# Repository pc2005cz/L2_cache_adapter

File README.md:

NOTICE this is just an untested proof of concept

# 486 L2 cache adapter for TSOP32/DIP32

Asynchronous fast SRAM chips in DIP32 package, were phased out. This makes not possible to use new chips to upgrade 486 L2 cache. However there are still compatible SRAM variants in SMT packages.

This project aims to create a PCB design, which allows the retro community to put TSOP32 chip into a DIP32 socket.

# Design

DIP32 sockets usually have the absolute maximum dimensions 10 x 40 mm. The adapter need to be less wide than that (and any exceeding PCB space due to a manufacturing tolerances needs to be sanded out).

TSOP32 type I chips needs to have width below this limit too. This reduces the list of possible chips only few types. Also there is a difference between 3.3V and 5V SRAM pinouts. The 3.3V pinouts would be highly complicated to route on 2 layer PCB.

The resulting list of chips I've found is:

* IS61C1024AL-12TLI
* CY7C109D-10ZXI
* AS7C1024B-12TCN

These chips have dimensions around 8 x 20 mm so there will be almost 1 mm between the side of the chip and the edge of the PCB (2 mm between chips on the motherboard).

Shorter variants seems to exist: IS61C1024AL-12HLI and AS7C1024B-10STC. These have dimensions 8 x 13.4 mm. The PCB could be changed in a way the pads for pins 17 to 32 will be closer to the upper part of the PCB.

Sadly a 1 mm space between chip and the PCB edge is not enough for having THT pins for the DIP32 socket. Only SMT pins can be placed below the SRAM TSOP package. If using a pin like this:

The top part needs to be cut and sanded to the wide section, which then needs to be soldered down in a similar way as the BGA or QFN is.

The THT section in the current version of the PCB is using hole size 0.8 mm. So the round/precise pins should fit (usually 0.6 mm). The square pinheader is not supported (it would destroyed the motherboard socket anyway).

All pin sections have extruding copper section nearing the center of the PCB. This should help with QFN-like soldering and it is also allowing for using a 90° angled pinheader.

BTW an older version of the PCB had "half-THT" holes below the TSOP chip, where the pin would end inside the PCB thickness and was soldered only on one side (no copper below the chip). Not sure if this design can be manufactured (essentially a half via), so I removed that.

# Design rules

* Precise (rounded) pinheaders have diameter: 0.47 mm to 0.6 mm
* Hole tolerance (for adapter pins) is: about +- 0.1 mm => THT pad hole diameter 0.8 mm
* Copper clearance to edge: >= 0.2 mm
* Pin mapping is not 1:1, the PCB cannot be used an arbitrary TSOP/DIP adapter

# Links

Sourcing the chips should be possible from Mouser, Digikey and TME, there are probably other sources too:

## IS61C1024AL-12TLI

[TME](https://www.tme.eu/cz/en/details/is61c1024al-12tli/parallel-sram-memories-integ-circ/issi/)
[Mouser](https://eu.mouser.com/ProductDetail/ISSI/IS61C1024AL-12TLI?qs=YdQ7Kj7W0bxK0kzoprU3Cw%3D%3D)
[Digikey](https://www.digikey.com/en/products/detail/issi-integrated-silicon-solution-inc/IS61C1024AL-12TLI/1557110)

## CY7C109D-10ZXI (it seems it is EOL)

[Mouser](https://eu.mouser.com/ProductDetail/Infineon-Technologies/CY7C109D-10ZXI?qs=QxhBKGBQLiLnC0p%252BIVeZeA%3D%3D)
[Digikey](https://www.digikey.com/en/products/detail/infineon-technologies/CY7C109D-10ZXI/1640242)

## AS7C1024B-12TCN

[TME](https://www.tme.eu/cz/en/details/as7c1024b-12tcn/parallel-sram-memories-integ-circ/alliance-memory/)
[Mouser](https://eu.mouser.com/ProductDetail/Alliance-Memory/AS7C1024B-12TCN?qs=E5c5%252Bmu3i39p9b7hUnTiBw%3D%3D)
[Digikey](https://www.digikey.com/en/products/detail/alliance-memory-inc/AS7C1024B-12TCN/4234602)

If you have a courage to make the adapter. Please share your experiences.

Licensed under CC BY-NC-SA 4.0

pc2005

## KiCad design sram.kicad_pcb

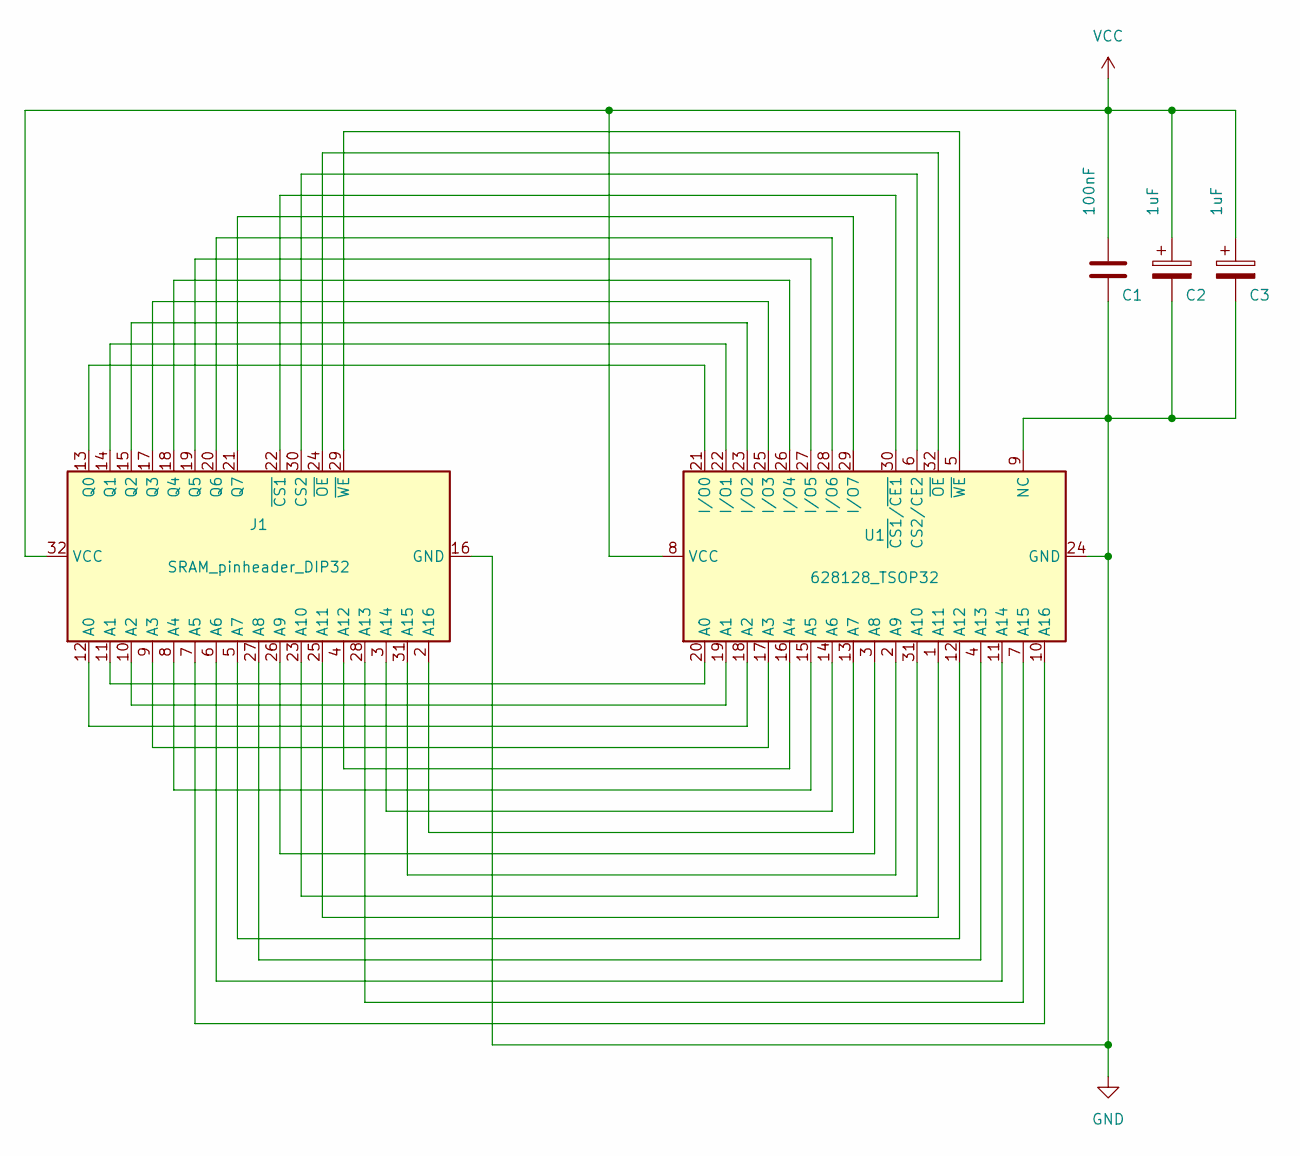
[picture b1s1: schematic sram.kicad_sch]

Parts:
C1: 100nF; C_0805_2012Metric
C2, C3: 1uF; C_0805_2012Metric
J1: SRAM_pinheader_DIP32; DIP-32_HYBRID_socket
U1: 628128_TSOP32; TSOP-I-32_18.4x8mm_P0.5mm_silkscreen_mod

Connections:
GND: C1.2, C2.2, C3.2, J1.16 (GND), U1.9 (NC), U1.24 (GND)
unnamed: J1.12 (A0), U1.18 (A2)
unnamed: J1.11 (A1), U1.20 (A0)
unnamed: J1.10 (A2), U1.19 (A1)
unnamed: J1.9 (A3), U1.17 (A3)
unnamed: J1.8 (A4), U1.15 (A5)
unnamed: J1.7 (A5), U1.10 (A16)
unnamed: J1.6 (A6), U1.11 (A14)
unnamed: J1.5 (A7), U1.12 (A12)
unnamed: J1.27 (A8), U1.4 (A13)
unnamed: J1.26 (A9), U1.3 (A8)
unnamed: J1.23 (A10), U1.31 (A10)
unnamed: J1.25 (A11), U1.1 (A11)
unnamed: J1.4 (A12), U1.16 (A4)
unnamed: J1.28 (A13), U1.7 (A15)
unnamed: J1.3 (A14), U1.14 (A6)
unnamed: J1.31 (A15), U1.2 (A9)
unnamed: J1.2 (A16), U1.13 (A7)
unnamed: J1.30 (CS2), U1.6 (CS2/CE2)
unnamed: J1.13 (Q0), U1.21 (I/O0)
unnamed: J1.14 (Q1), U1.22 (I/O1)
unnamed: J1.15 (Q2), U1.23 (I/O2)
unnamed: J1.17 (Q3), U1.25 (I/O3)
unnamed: J1.18 (Q4), U1.26 (I/O4)
unnamed: J1.19 (Q5), U1.27 (I/O5)
unnamed: J1.20 (Q6), U1.28 (I/O6)
unnamed: J1.21 (Q7), U1.29 (I/O7)
unnamed: J1.22 (~CS1), U1.30 (~CS1/~CE1)
unnamed: J1.24 (~OE), U1.32 (~OE)
unnamed: J1.29 (~WE), U1.5 (~WE)
VCC: C1.1, C2.1, C3.1, J1.32 (VCC), U1.8 (VCC)

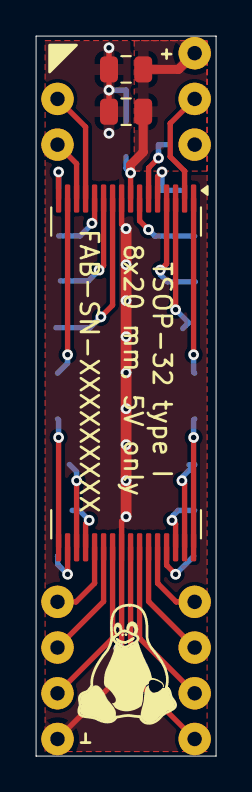
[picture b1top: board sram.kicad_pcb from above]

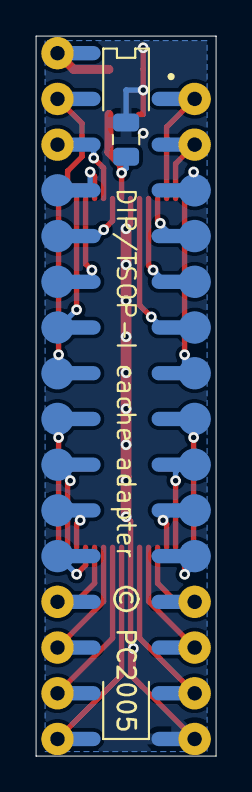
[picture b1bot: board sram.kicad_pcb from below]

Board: 2 copper layers, 10.0 x 40.0 mm, 5 parts (2 on the bottom side), 31 nets.

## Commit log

2025-10-01 TSOP32 to DIP32 adapter
    Initial commit
2025-10-02 Added sources for the SRAM chips
2025-10-02 Better labels for decoupling caps
    Added DIP pinheader 3D model

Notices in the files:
sram.kicad_pcb:
© PC2005
